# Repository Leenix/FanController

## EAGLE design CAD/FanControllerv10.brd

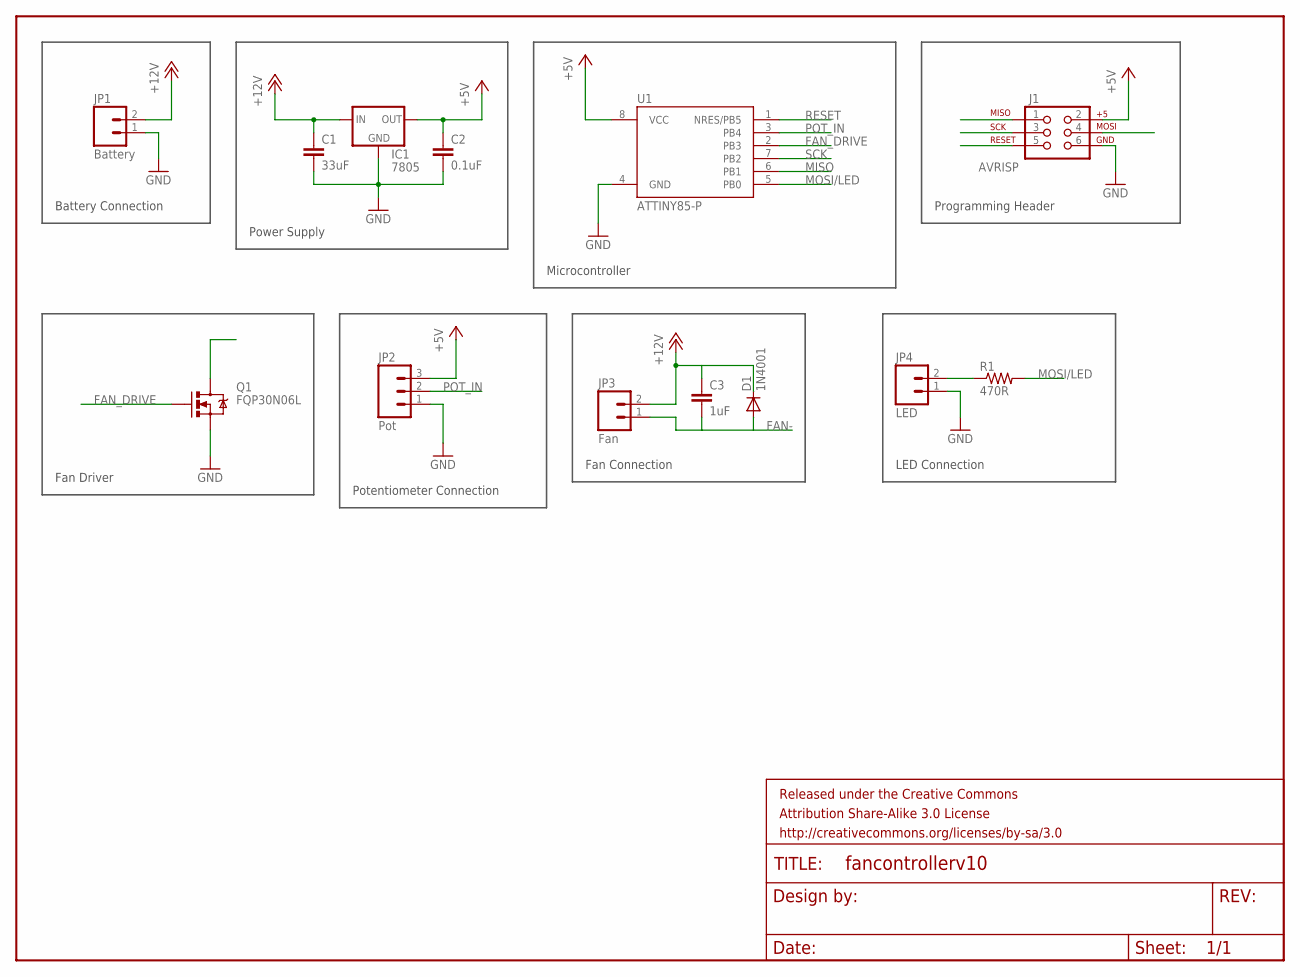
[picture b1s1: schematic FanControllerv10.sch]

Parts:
C1: 33uF; CAP-PTH-SMALL
C2: 0.1uF; CAP-PTH-SMALL
C3: 1uF; CAP-PTH-SMALL
D1: 1N4001; DIODE-1N4148
FRAME1: FRAME-LETTER; CREATIVE_COMMONS
IC1: 7805; 78XXL
J1: AVRISP; 2X3
JP1: Battery; 1X02
JP2: Pot; 1X03
JP3: Fan; 1X02
JP4: LED; 1X02
Q1: FQP30N06L; TO220V
R1: 470R; 1206
U1: ATTINY85-P; PDIP08_300MIL

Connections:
+5V: C2.1, IC1.OUT, J1.2, JP2.3, U1.8 (VCC)
+12V: C1.1, C3.1, D1.C, IC1.IN, JP1.2, JP3.2
FAN-: C3.2, D1.A, JP3.1, Q1.2 (D)
FAN_DRIVE: Q1.1 (G), U1.2 (PB3)
GND: C1.2, C2.2, IC1.GND, J1.6, JP1.1, JP2.1, JP4.1, Q1.3 (S), U1.4 (GND)
MISO: J1.1, U1.6 (PB1)
MOSI/LED: J1.4, R1.2, U1.5 (PB0)
unnamed: JP4.2, R1.1
POT_IN: JP2.2, U1.3 (PB4)
RESET: J1.5, U1.1 (NRES/PB5)
SCK: J1.3, U1.7 (PB2)

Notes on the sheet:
Power Supply
Fan Driver
Potentiometer Connection
Programming Header
Battery Connection
Fan Connection
Microcontroller
LED Connection

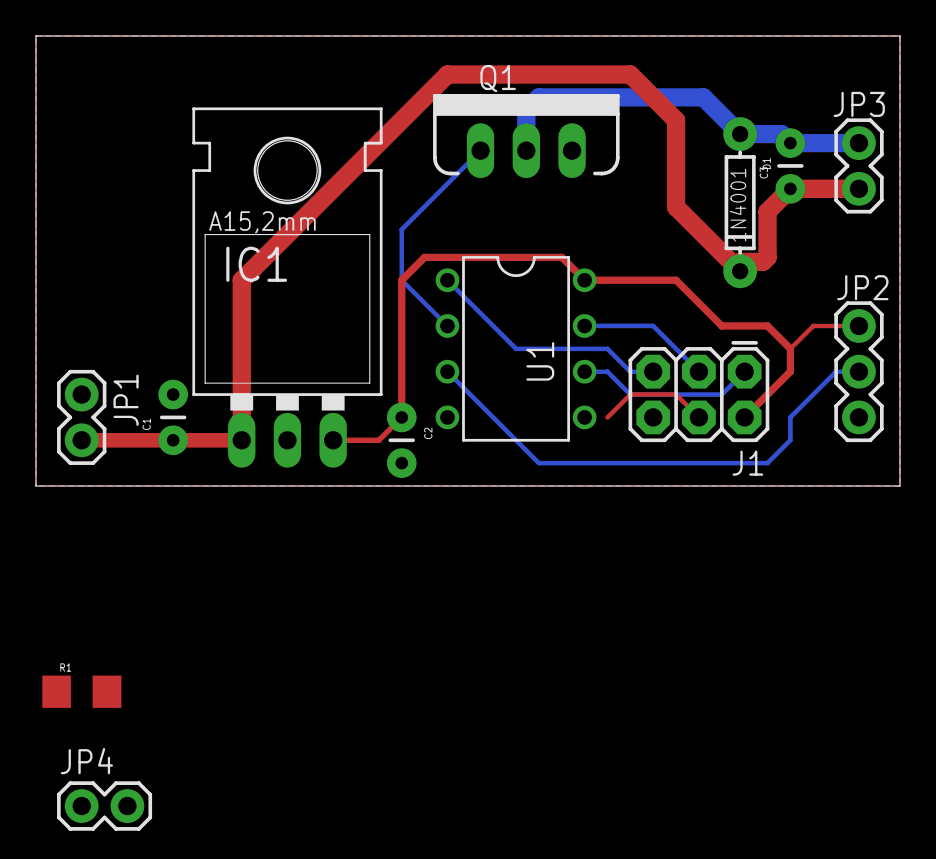
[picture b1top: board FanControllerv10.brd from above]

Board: 2 copper layers, 48.0 x 25.0 mm, 14 parts (0 on the bottom side), 11 nets.

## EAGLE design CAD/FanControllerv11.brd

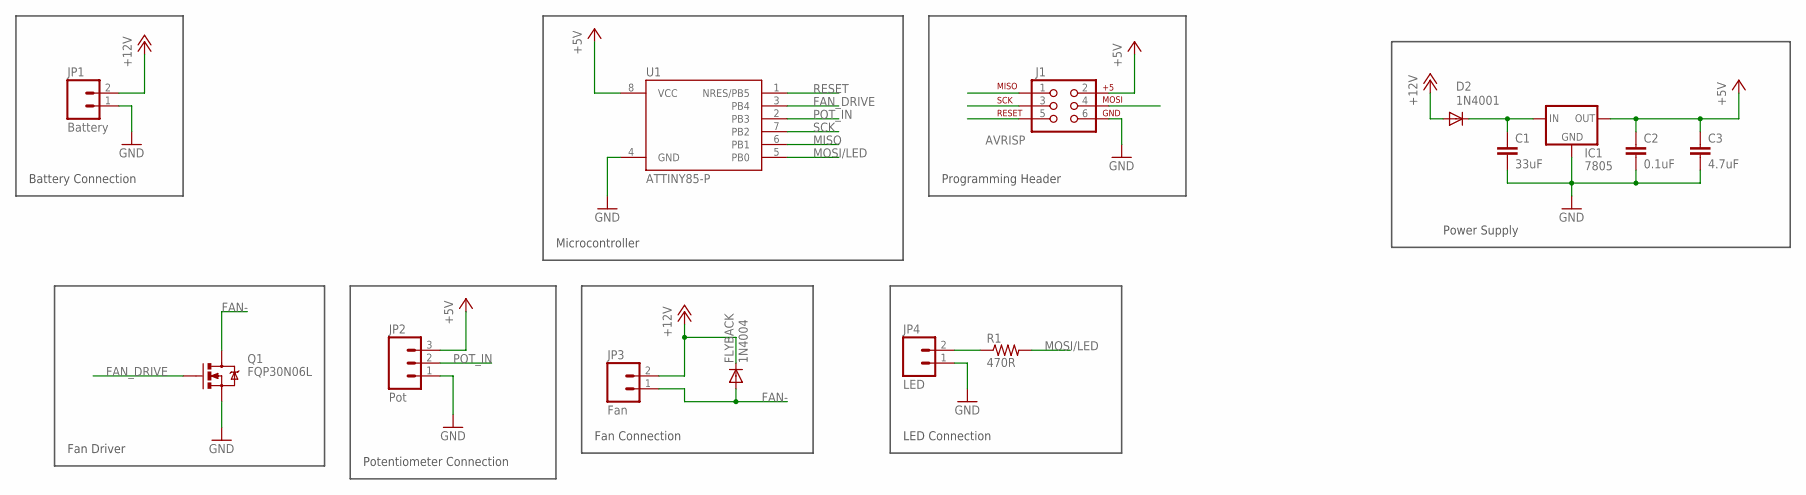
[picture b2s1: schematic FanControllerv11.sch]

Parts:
C1: 33uF; CAP-PTH-SMALL
C2: 0.1uF; CAP-PTH-LARGE
C3: 4.7uF; CAP-PTH-SMALL
D2: 1N4001; DIODE-1N4148
FLYBACK: 1N4004; DIODE-1N4148
IC1: 7805; 78XXL
J1: AVRISP; 2X3
JP1: Battery; 1X02_XTRA_BIG
JP2: Pot; MOLEX-1X3
JP3: Fan; 1X02_XTRA_BIG
JP4: LED; MOLEX-1X2
Q1: FQP30N06L; TO220V
R1: 470R; AXIAL-0.3
U1: ATTINY85-P; PDIP08_300MIL

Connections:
+5V: C2.1, C3.1, IC1.OUT, J1.2, JP2.3, U1.8 (VCC)
+12V: D2.A, FLYBACK.C, JP1.2, JP3.2
FAN-: FLYBACK.A, JP3.1, Q1.2 (D)
FAN_DRIVE: Q1.1 (G), U1.3 (PB4)
GND: C1.2, C2.2, C3.2, IC1.GND, J1.6, JP1.1, JP2.1, JP4.1, Q1.3 (S), U1.4 (GND)
MISO: J1.1, U1.6 (PB1)
MOSI/LED: J1.4, R1.P$2 (2), U1.5 (PB0)
unnamed: JP4.2, R1.P$1 (1)
unnamed: C1.1, D2.C, IC1.IN
POT_IN: JP2.2, U1.2 (PB3)
RESET: J1.5, U1.1 (NRES/PB5)
SCK: J1.3, U1.7 (PB2)

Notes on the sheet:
Power Supply
Fan Driver
Potentiometer Connection
Programming Header
Battery Connection
Fan Connection
Microcontroller
LED Connection

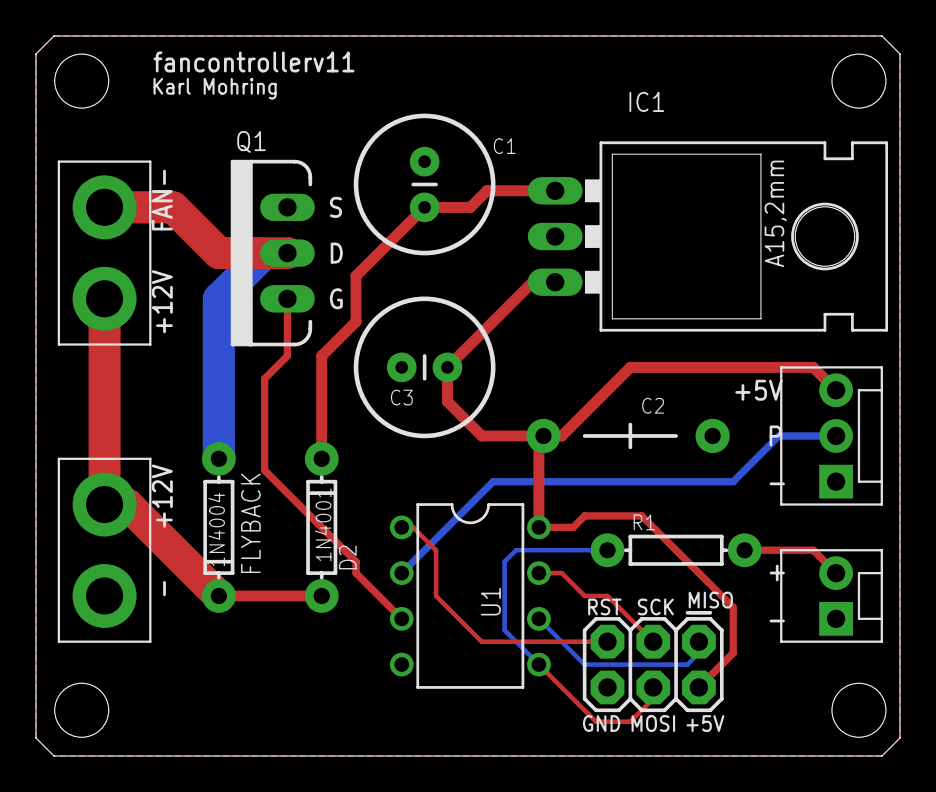
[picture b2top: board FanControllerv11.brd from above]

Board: 2 copper layers, 48.0 x 40.0 mm, 14 parts (0 on the bottom side), 12 nets.

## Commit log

2015-01-27 :neckbeard: Added .gitattributes & .gitignore files
2015-01-27 Initial commit - Finished project

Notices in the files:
parts and their libraries:
SparkFun-PowerIC: Licensing: CC v3.0 Share-Alike You are welcome to use this library for commercial purposes.
SparkFun-Aesthetics: Released under the Creative Commons Attribution Share-Alike 3.0 License
SparkFun-Aesthetics: http://creativecommons.org/licenses/by-sa/3.0
